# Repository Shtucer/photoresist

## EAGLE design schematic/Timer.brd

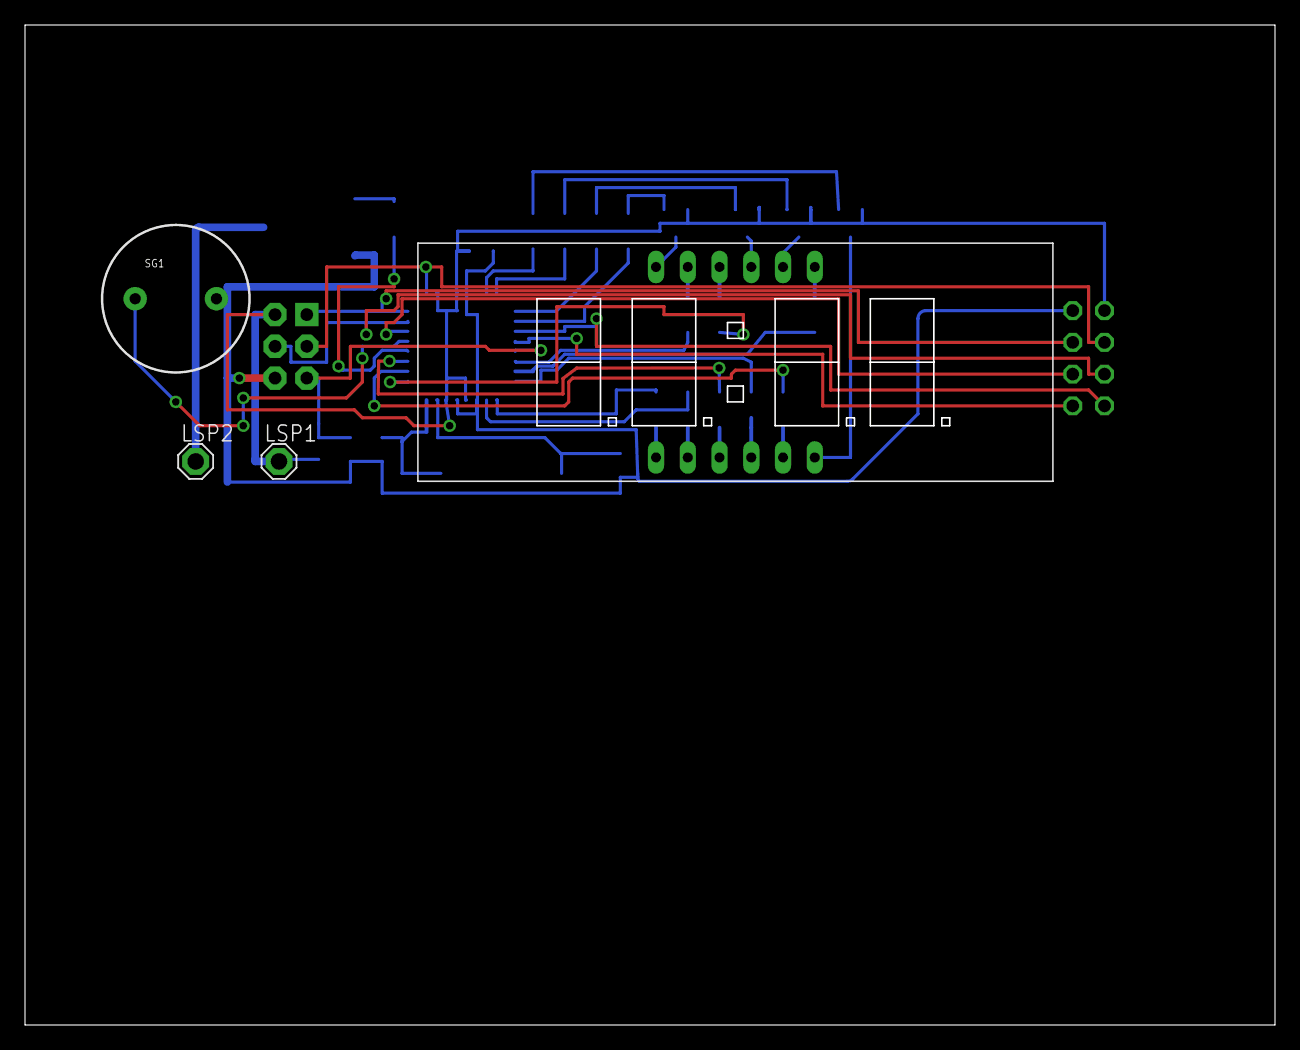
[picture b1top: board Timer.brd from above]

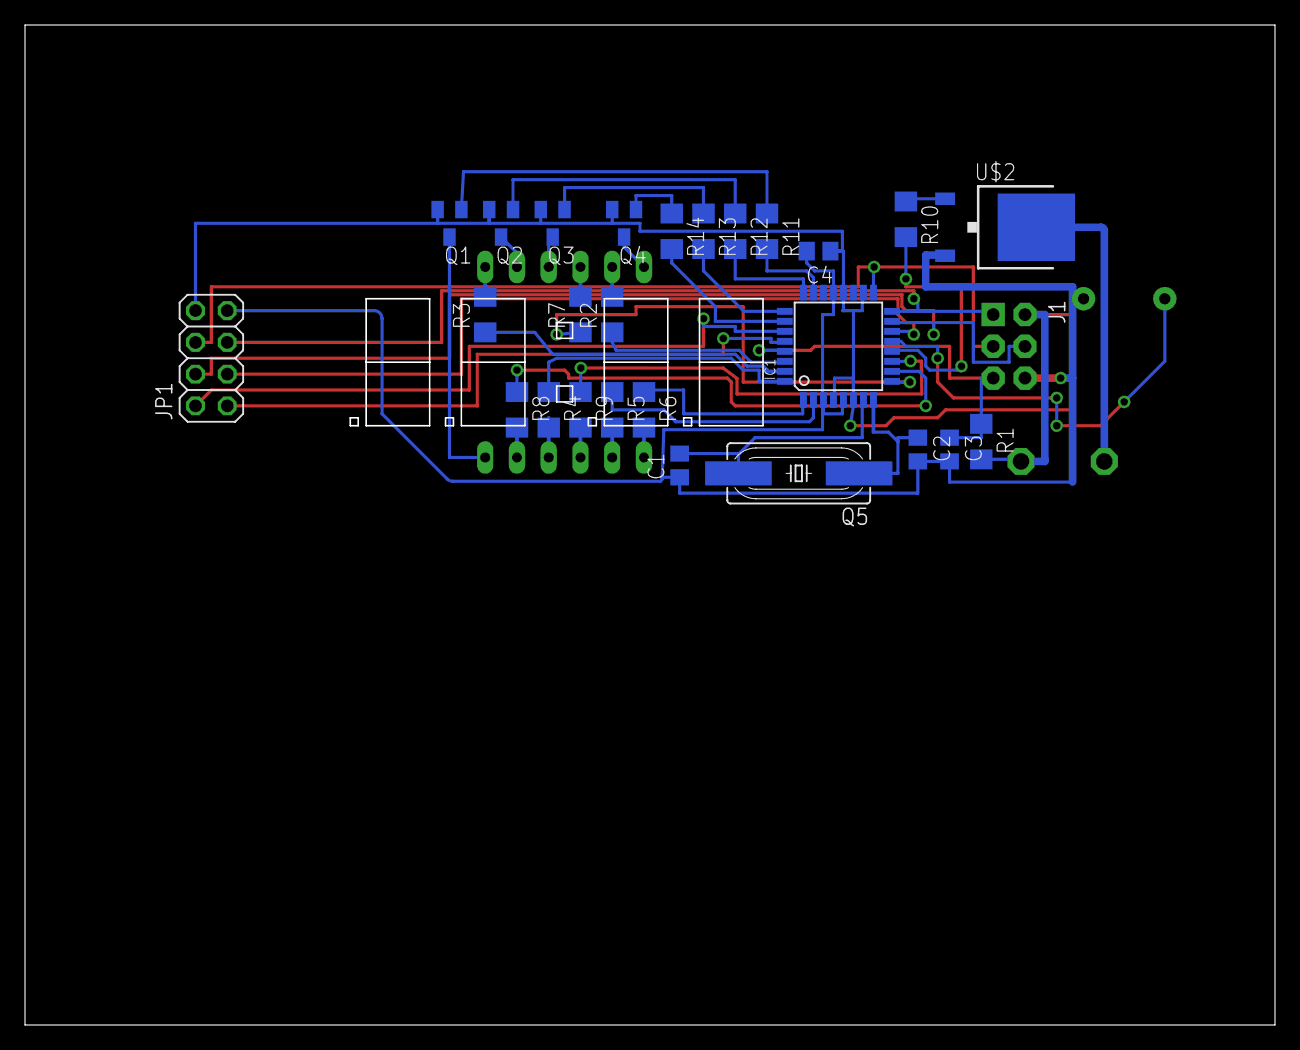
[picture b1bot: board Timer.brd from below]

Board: 2 copper layers, 99.9 x 79.9 mm, 31 parts (27 on the bottom side), 43 nets.

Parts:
C1, C2: 22p; C0805
C3, C4: 0.1; C0805
IC1: MEGA8-AI; TQFP32-08
J1: AVR_SPI_PRG_6NS; 2X3-NS
JP1: 2X04
LSP1, LSP2: SE13
Q1, Q2, Q3, Q4: BC807-40SMD; SOT23-BEC
Q5: HC49UP
R1, R11, R12, R13, R14: 1k5; R1206
R2, R3, R4, R5, R6, R7, R8, R9: 330; R1206
R10: 10k; R1206
SG1: BUZZERPTH-KIT; BUZZER-12MM-KIT
U$1: FYG-5564BUG; FYQ-5643XX
U$2: P0903BDG; TO252

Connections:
A: IC1.30, R2.1
B: IC1.31, R3.1
BUZZ: IC1.13, SG1.-
C: IC1.32, R4.1
CTA1: IC1.26, R14.2
CTA2: IC1.25, R13.2
CTA3: IC1.24, R12.2
CTA4: IC1.23, R11.2
D: IC1.2, R5.1
DP: IC1.11, R9.1
E: IC1.1, R6.1
F: IC1.9, R7.1
G: IC1.10, R8.1
GND: C1.1, C2.2, C3.2, C4.2, IC1.3, IC1.5, IC1.21, J1.6, JP1.7, SG1.+, U$2.3
LED1: IC1.16, J1.1, JP1.5
LED2: IC1.17, J1.3, JP1.6
unnamed: Q1.C, U$1.COMM4
unnamed: Q2.C, U$1.COMM3
unnamed: Q3.C, U$1.COMM2
unnamed: Q4.C, U$1.COMM1
unnamed: C1.2, IC1.7, Q5.2
unnamed: C2.1, IC1.8, Q5.1
unnamed: R10.1, U$2.1
unnamed: R2.2, U$1.A
unnamed: R3.2, U$1.B
unnamed: R4.2, U$1.C
unnamed: R5.2, U$1.D
unnamed: R6.2, U$1.E
unnamed: R7.2, U$1.F
unnamed: R8.2, U$1.G
unnamed: R9.2, U$1.DP
unnamed: LSP2.MP, U$2.2
unnamed: Q3.B, R13.1
unnamed: Q1.B, R11.1
unnamed: Q2.B, R12.1
unnamed: Q4.B, R14.1
RELAY: IC1.12, R10.2
RST: C3.1, IC1.29, J1.5, R1.1
SW1: IC1.28, JP1.1
SW2: IC1.27, JP1.2
SW3: IC1.14, JP1.3
SW4: IC1.15, J1.4, JP1.4
VCC: C4.1, IC1.4, IC1.6, IC1.18, IC1.20, J1.2, JP1.8, LSP1.MP, Q1.E, Q2.E, Q3.E, Q4.E, R1.2

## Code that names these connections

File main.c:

/*
 * main.c
 *
 *  Created on: 27 ���. 2015 �.
 *      Author: Shtucer
 */
//#define F_CPU	12000000UL

#include <avr/io.h>

#include <util/delay.h>
#include <avr/interrupt.h>

#include "seg_defines.h"
#include "config.h"


// Video memory
unsigned char data[4] = {0,0,0,0};
unsigned int exposeTime = 0;

#define relayIsOn() (PINB & PB0)




#define IDLE			0
#define EXPOSE			1
#define SETUP			3


/*
#define MINUTES_SETUP 	2
#define SECONDS_SETUP 	3
*/



volatile int	STATUS = IDLE;

// Update display
ISR(TIMER0_OVF_vect){
	static unsigned char count=0;
#ifdef DEBUG
	static char totalOVF=0;
	if(totalOVF>=0){
#endif

	PORTC ^= _BV(count);
	count = (count+1)%4;
	PORTD = data[count];
	PORTC = ~_BV(count);

#ifdef DEBUG
	totalOVF=0;
	}
	totalOVF++;
#endif

}

// Expose timer
ISR(TIMER1_COMPA_vect){
	if((STATUS & EXPOSE) && (exposeTime > 1))
	{
		exposeTime -= 1;
	}
	else
	{
		exposeTime = 0;
		STATUS = IDLE;
	}
}

// Check the Buttons
ISR(TIMER2_OVF_vect){
	if(IsPressed(SW1)){
		PORTC |= _BV(PC4);

	}
	else {
		PORTC &= ~_BV(PC4);
	}
}



void setup_io(){
	ACSR |= (1 << ACD);

	// Cathodes pins to output mode
	DDRC |= 1 << PC0; // CTA4
	DDRC |= 1 << PC1; // CTA3
	DDRC |= 1 << PC2; // CTA2
	DDRC |= 1 << PC3; // CTA1

	// Cathodes pins to HIGH (0 - ON, 1 - OFF)
	PORTC |= (1 << PC0);
	PORTC |= (1 << PC1);
	PORTC |= (1 << PC2);
	PORTC |= (1 << PC3);

	DDRC |= 1 << PC5;
	DDRC |= 1 << PC4;
	PORTC |= (0 << PC5) | (0 << PC4);

	DDRB |= (1 << RELAY);
	PORTB &= ~(1 << RELAY);


	DDRB |= 0 << SW1;
	DDRB |= 0 << SW2;
	DDRB |= 0 << SW3;
	DDRB |= 0 << SW4;

	// Buttons pullup
	PORTB &= ~(1 << SW1); // SW1
	PORTB &= ~(1 << SW2); // SW2
	PORTB &= ~(1 << SW3); // SW3
	PORTB &= ~(1 << SW4); // SW4

	// Anodes (segments) pins to output
	DDRD |= 1 << PD0; // A
	DDRD |= 1 << PD1; // B
	DDRD |= 1 << PD2; // C
	DDRD |= 1 << PD3; // E
	DDRD |= 1 << PD4; // D
	DDRD |= 1 << PD5; // F
	DDRD |= 1 << PD6; // G
	DDRD |= 1 << PD7; // dp

	// Anodes (segments) pins to HIGH  (0 - ON, 1 - OFF)
	PORTD = 0xff; //0b11111111; // OFF all segments


}

void startButtonTimer(){
	// Timer2 - button events
	// every 1ms
	// /8 prescaler
	ASSR |= (0 << AS2); // Connect timer to TOSC1
	TCCR2 |=  (0 << CS22) | (1 << CS21) | (1 << CS20);
	TCNT2 = 47;
	TIMSK |= (1 << TOIE2);
}

void startDisplayUpdateTimer(){
#ifdef DEBUG
	TCNT0 = 220;
#else
	TCNT0 = 0;
#endif

	// Timer0 - display update
	// /8 prescaler
	TCCR0 |=  (0 << CS02) | (1 << CS01) | (0 << CS00);
	// start timer0
	TIMSK |= (1 << TOIE0);

}

void stopExpositionTimer() {
	TIMSK &= ~(1 << OCIE1A);
}

void startExpositionTimer() {
	// Start timer 0x2DC6
	// Timer1 - time counter (every 1sec)
	// Prescaler 1024
	TCCR1B |= (1 << CS02) | (0 << CS01) | (1 << CS00);
	TCCR1B |= (1 << WGM12); // configure timer1 for CTC mode
	//OCR1A = 0x2dc6;
	OCR1A = (F_CPU/(2*1024))-1;

	TIMSK |= (1 << OCIE1A);
}
/*
void _display_digit(int pos, int dig){


	PORTC = _BV(POS[pos]);
//	PORTD = 0x00;
//	PORTC |= ((1<<PC0) | (1<<PC1) | (1<<PC2) | (1<<PC3));

	PORTD = dig;

	//_delay_ms(10);
	//PORTC |= (1 << POS[pos]);
	//PORTC |= (1 << POS[pos]);
}

void display(int integer){
		_display_digit(0, data[0]);
		_display_digit(1, data[1]);
		_display_digit(2, data[2]);
		_display_digit(3, data[3]);

}
*/

void display(int i){
	data[0] = DIGITS[i % 10];
	data[1] = DIGITS[(i/10)%10];
	data[2] = DIGITS[(i/100)%10];
	data[3] = DIGITS[(i/1000)];
}


int main(void){
//	cli();
	setup_io();

	STATUS = IDLE;
	startDisplayUpdateTimer();
	startButtonTimer();

	sei();

	while(1){
		switch(STATUS){
		case IDLE:
			break;
		case EXPOSE:
			if(relayIsOn()) {

			}
			break;
		case 	SETUP:
			break;
		default:
			break;
		}


	}
	return 0;
}

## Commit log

2015-11-09 Init commit
2015-11-09 изменения в схеме
2015-11-15 Scheme changed: swap pins
2015-11-15 заменил транзистор в схеме для эмулятора
2015-11-15 Decomposition files
2015-11-15 Decompose files

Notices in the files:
parts and their libraries:
SparkFun-Connectors: Licensing: Creative Commons ShareAlike 4.0 International - https://creativecommons.org/licenses/by-sa/4.0
